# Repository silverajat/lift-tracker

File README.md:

# lift-tracker

A wrist wearable that counts reps, measures rep speed and quality, buzzes when a set has slowed too much or rest is over, and tells me when to add weight. The moment a set ends, the phone app shows the rep count and a quality score for each rep (speed, range, consistency). The same signal pipeline is also built in Verilog as an RTL project, verified against a Python golden model on my own gym data.

**Status:** D1 logger running on the XIAO in the printed pod (battery, auto-recording, USB dumps). Now: Bluetooth control from a phone app, so each set is started, stopped and labelled from the phone. Custom PCB v1.1 ready to order. The final Fitbit-sized pod v2 (7 mm thick, charges on the Fitbit Air charger) is designed and routed, waiting on nRF module stock: see `hardware/pod-v2/`.

*Pod v4: XIAO nRF52840 Sense + LiPo in a black PETG print, on a hook-and-loop strap, charging over USB-C through the side hole.*

## Layout

```
firmware/   Zephyr firmware for the XIAO nRF52840 Sense
  logger/     D1: records IMU data to flash, dumps CSV over USB
python/     golden model and analysis of my lift data
  tools/      dump_logs.py: pulls recordings off the board
hardware/   enclosure CAD (OpenSCAD), STLs, later the KiCad PCB
rtl/        Verilog + cocotb tests + formal proofs
app/        the phone app (later, D6)
docs/       logo, accuracy report, photos, demo video
data/       recordings (raw data is git-ignored)
```

## Build order

**Device:** D0 parts → D1 logger → D2 record lifts → D3 Python model → D4 video check → D5 real firmware + Bluetooth → D6 app → D7 buzz alerts → D8 custom PCB → D9 bring-up.

**RTL:** R1 UART + cocotb → R2 full pipeline → R3 formal proofs → R4 FPGA demo.

The full plan lives in my Lift Tracker Wearable doc.

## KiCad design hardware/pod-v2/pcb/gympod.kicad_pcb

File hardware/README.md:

# Hardware

## pod/ — gym prototype enclosure

OpenSCAD source (`lift_pod.scad`, all sizes are parameters at the top) and print-ready STLs for the base, separator and lid. Holds the XIAO nRF52840 Sense and a 302030 LiPo; a one-piece 20 mm loop band threads through a channel underneath.

Print: PETG (PLA for fit tests), 0.16–0.2 mm layers, 3 walls, no supports. Base floor-down with a brim, lid dome-up, separator flat.

To change a size: edit the number in `lift_pod.scad`, render (F6), export STL.

## pod-v2/ — the final, Fitbit-sized pod

36.2 × 20.2 × 7.0 mm. A custom 4-layer board (nRF52840 module, BMI270 IMU, 2 MB flash, 40 mAh LiPo, coin motor) that charges on the Google Fitbit Air charger. The board is the pod's underside: two gold contacts 18 mm apart plus a steel disc for the charger's magnet, with a bridge so it charges either way round. Everything else goes over Bluetooth.

- `SPEC.md`: decisions, circuit, pin map, parts, assembly.
- `pcb/`: the whole board as Python data (`design.py`, `placement.py`) → KiCad schematic, placement, staged Freerouting, DRC (`make_release.sh`).
- `release/liftpod_v2_revA/`: Gerbers, JLC BOM/CPL, renders, schematic PDF, checks, `README_ORDER.md`.
- `lift_pod_v2.scad` / `lift_pod_v2_shell.stl`: the one-piece shell for JLC3DP (SLA black resin).

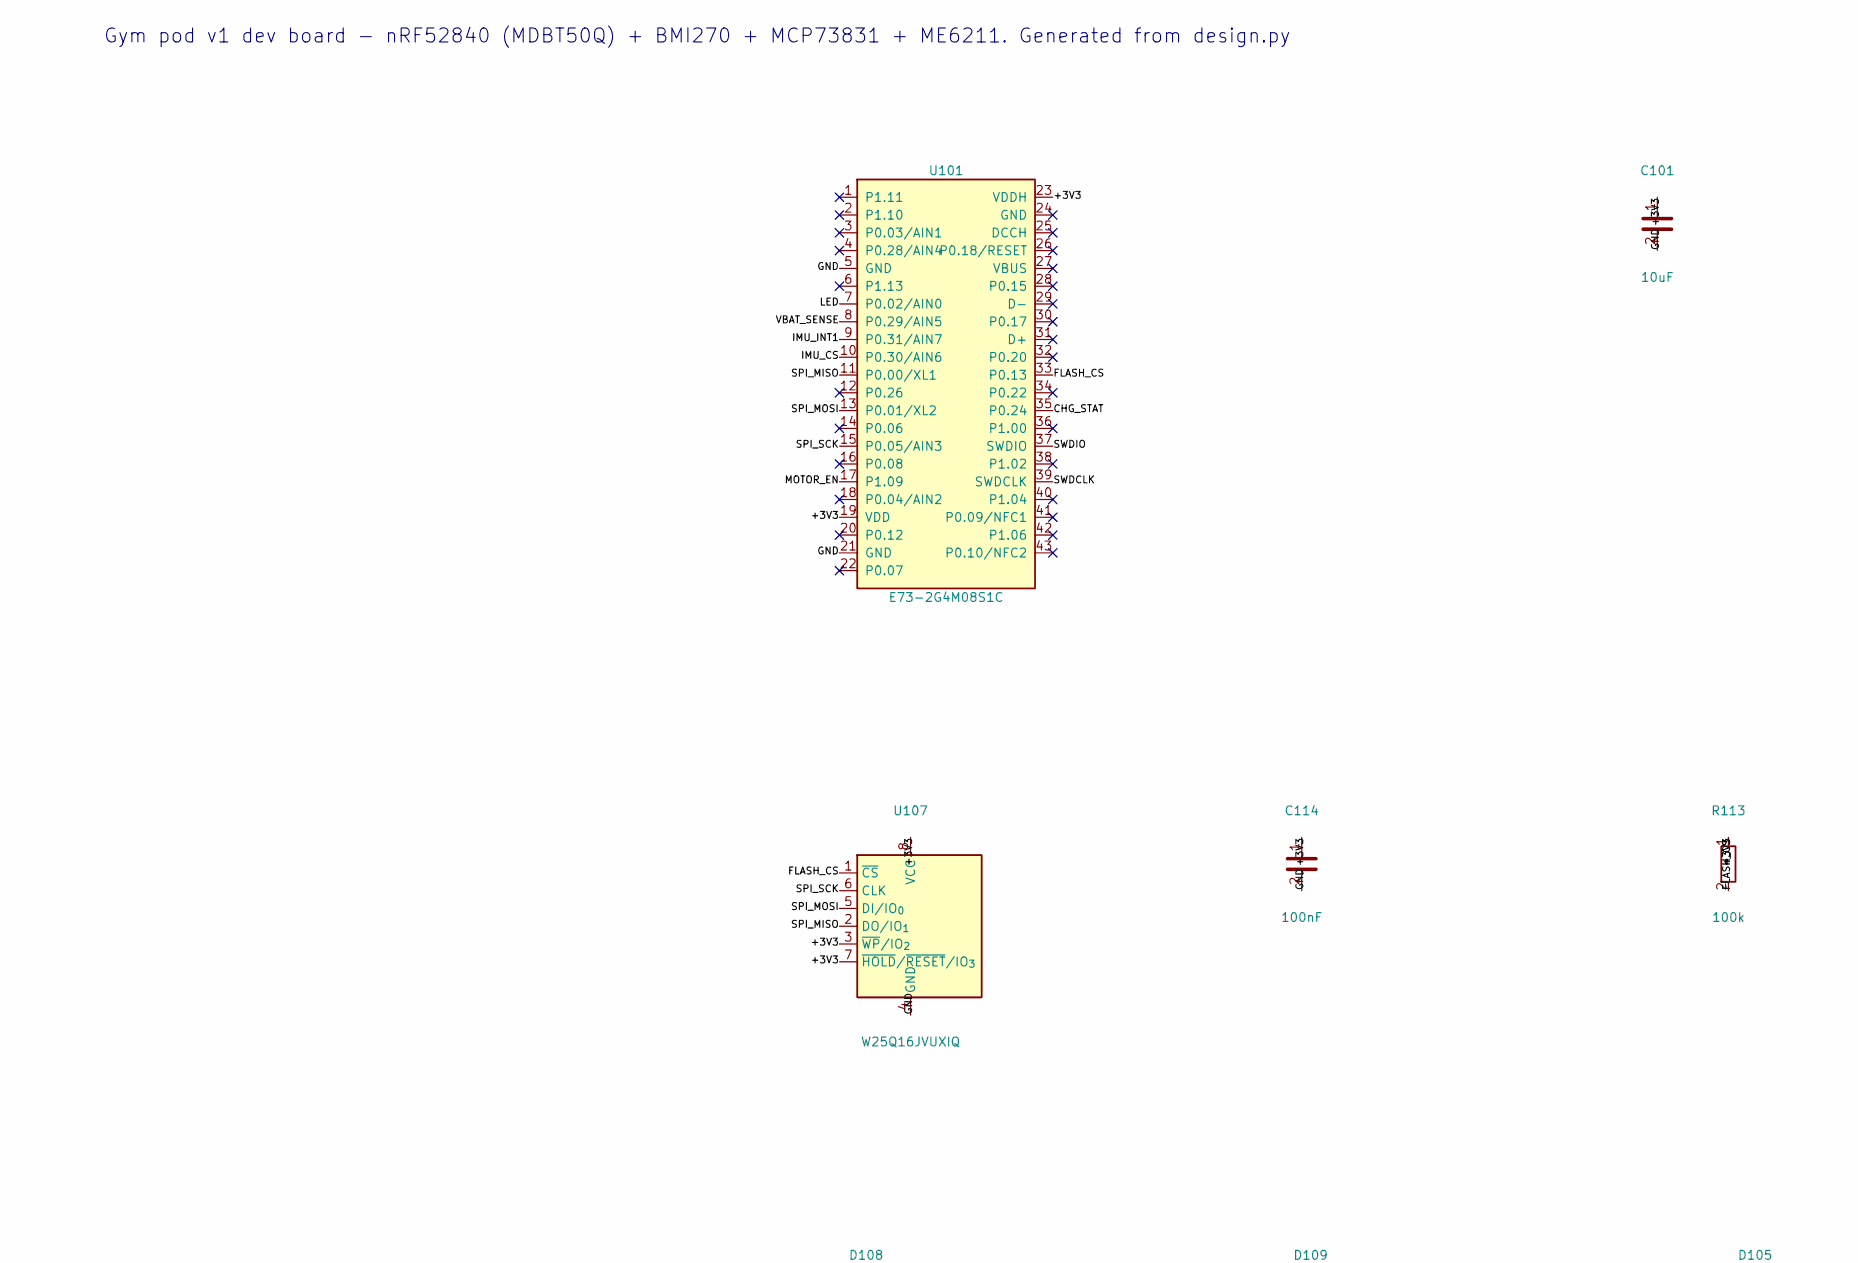
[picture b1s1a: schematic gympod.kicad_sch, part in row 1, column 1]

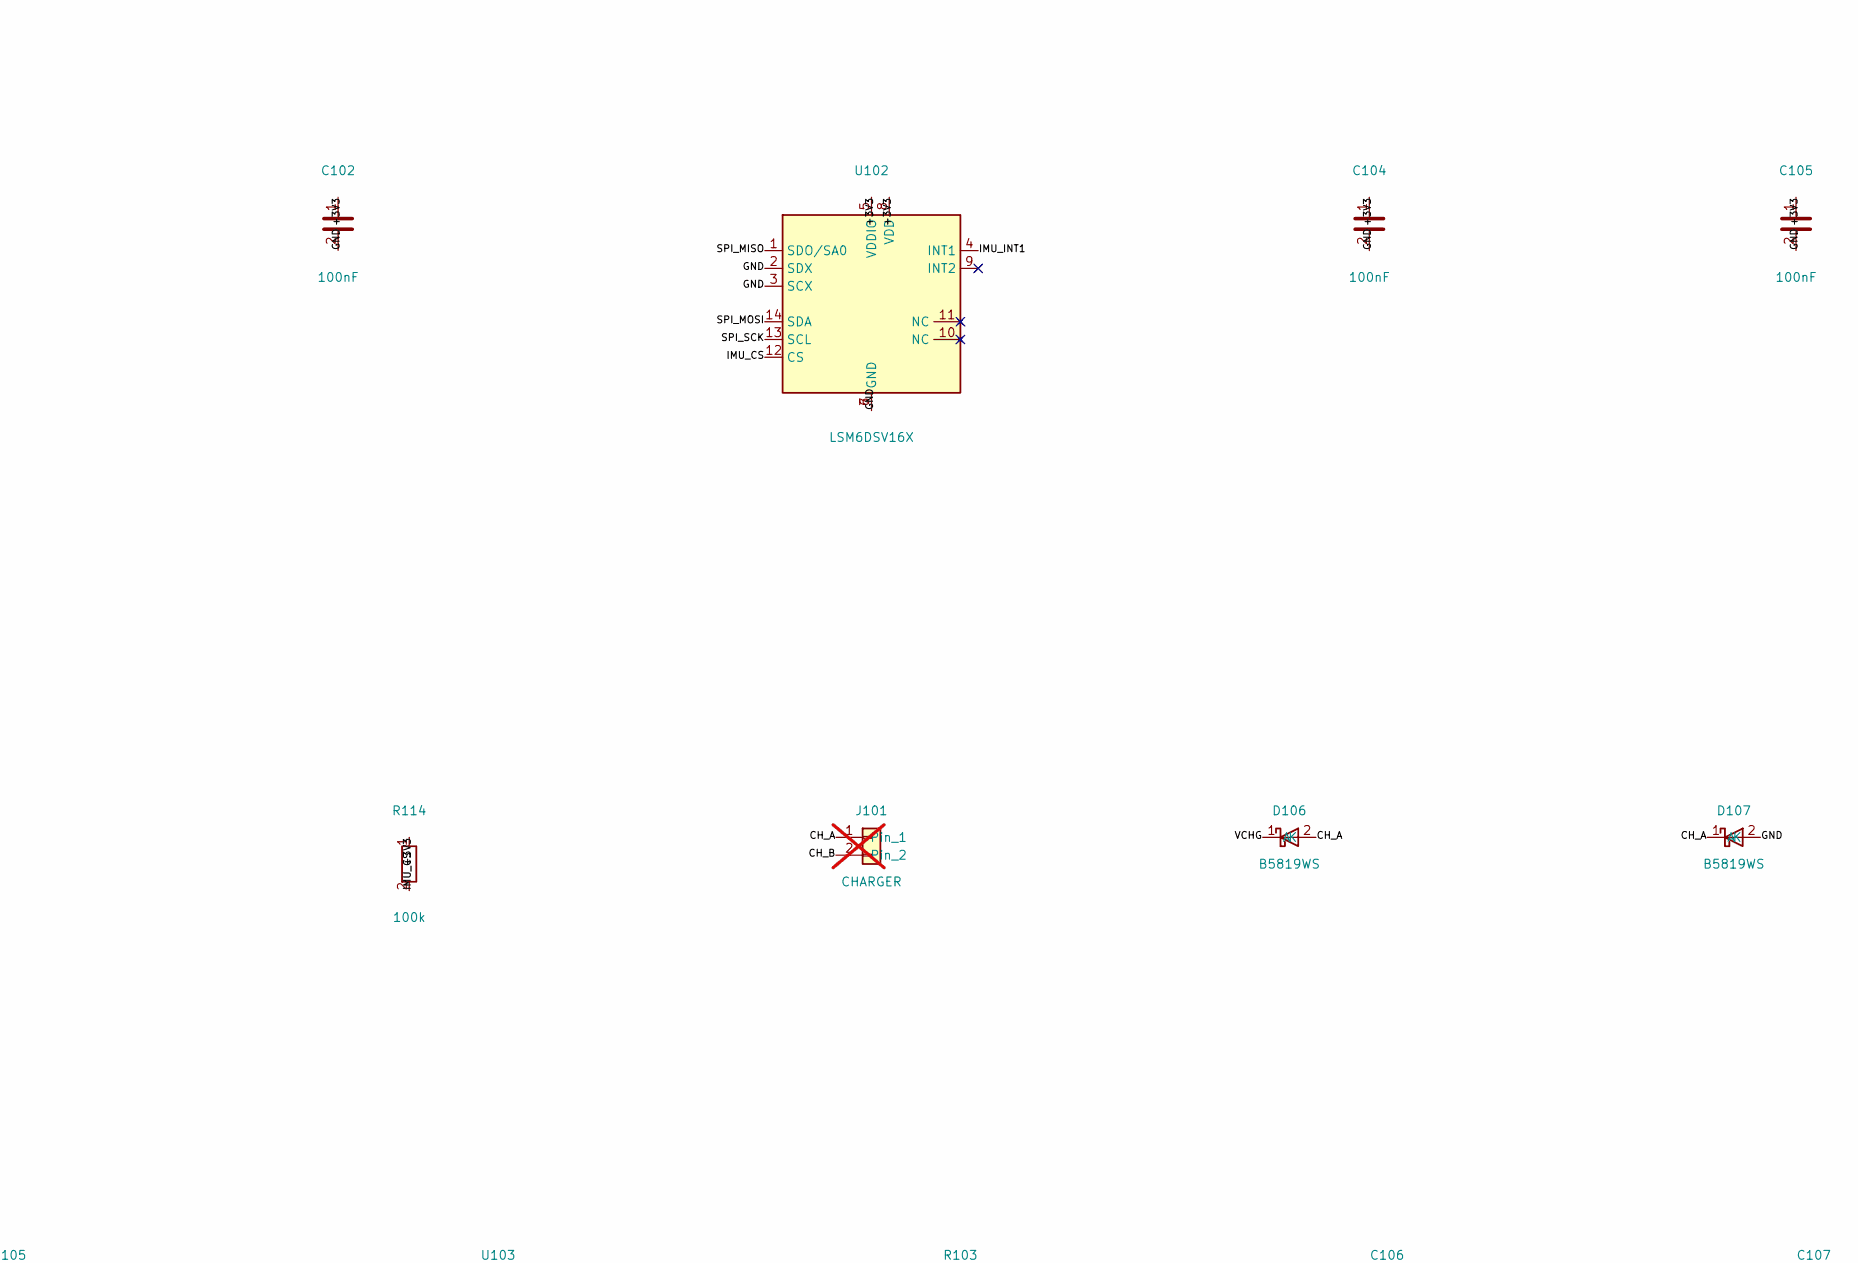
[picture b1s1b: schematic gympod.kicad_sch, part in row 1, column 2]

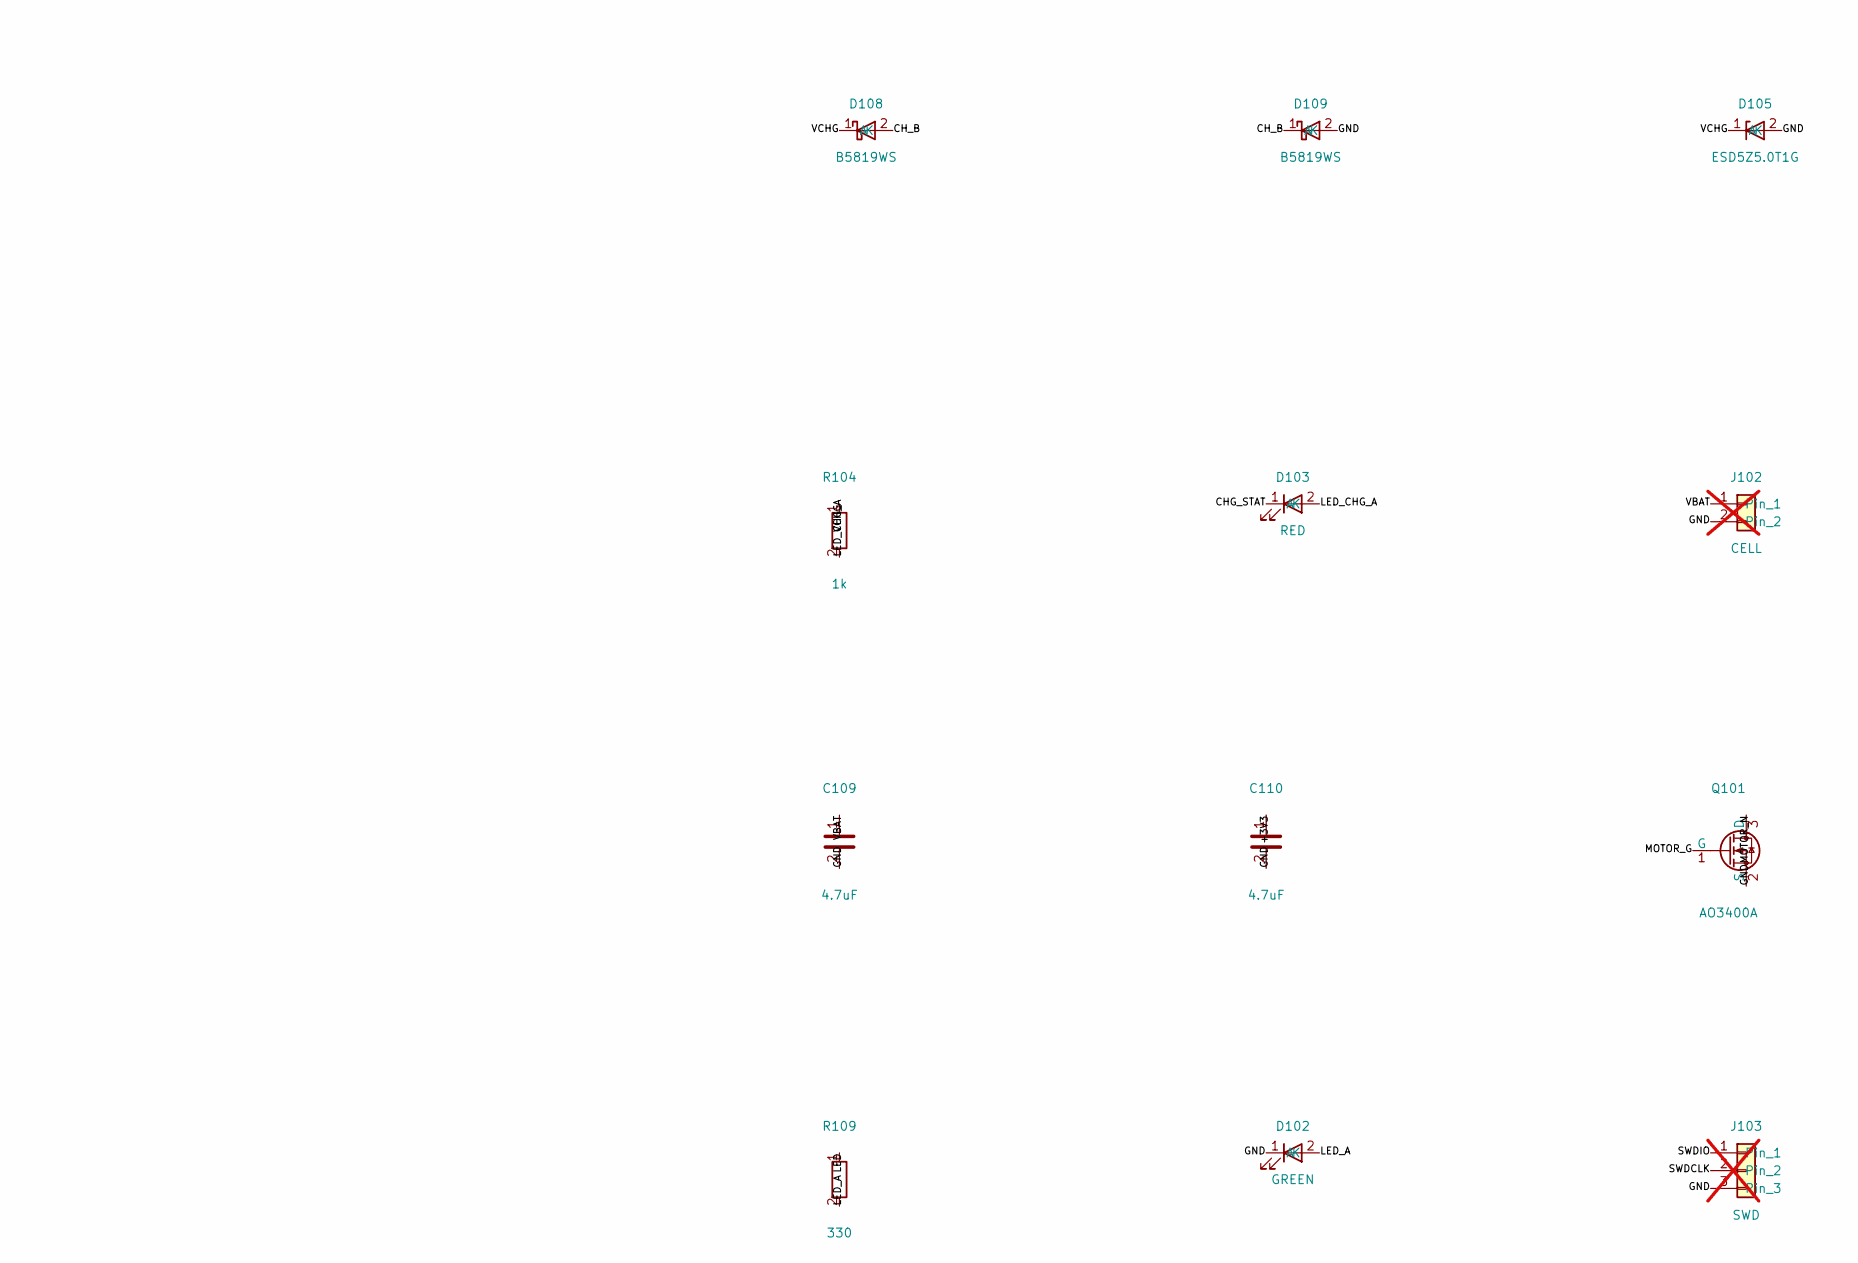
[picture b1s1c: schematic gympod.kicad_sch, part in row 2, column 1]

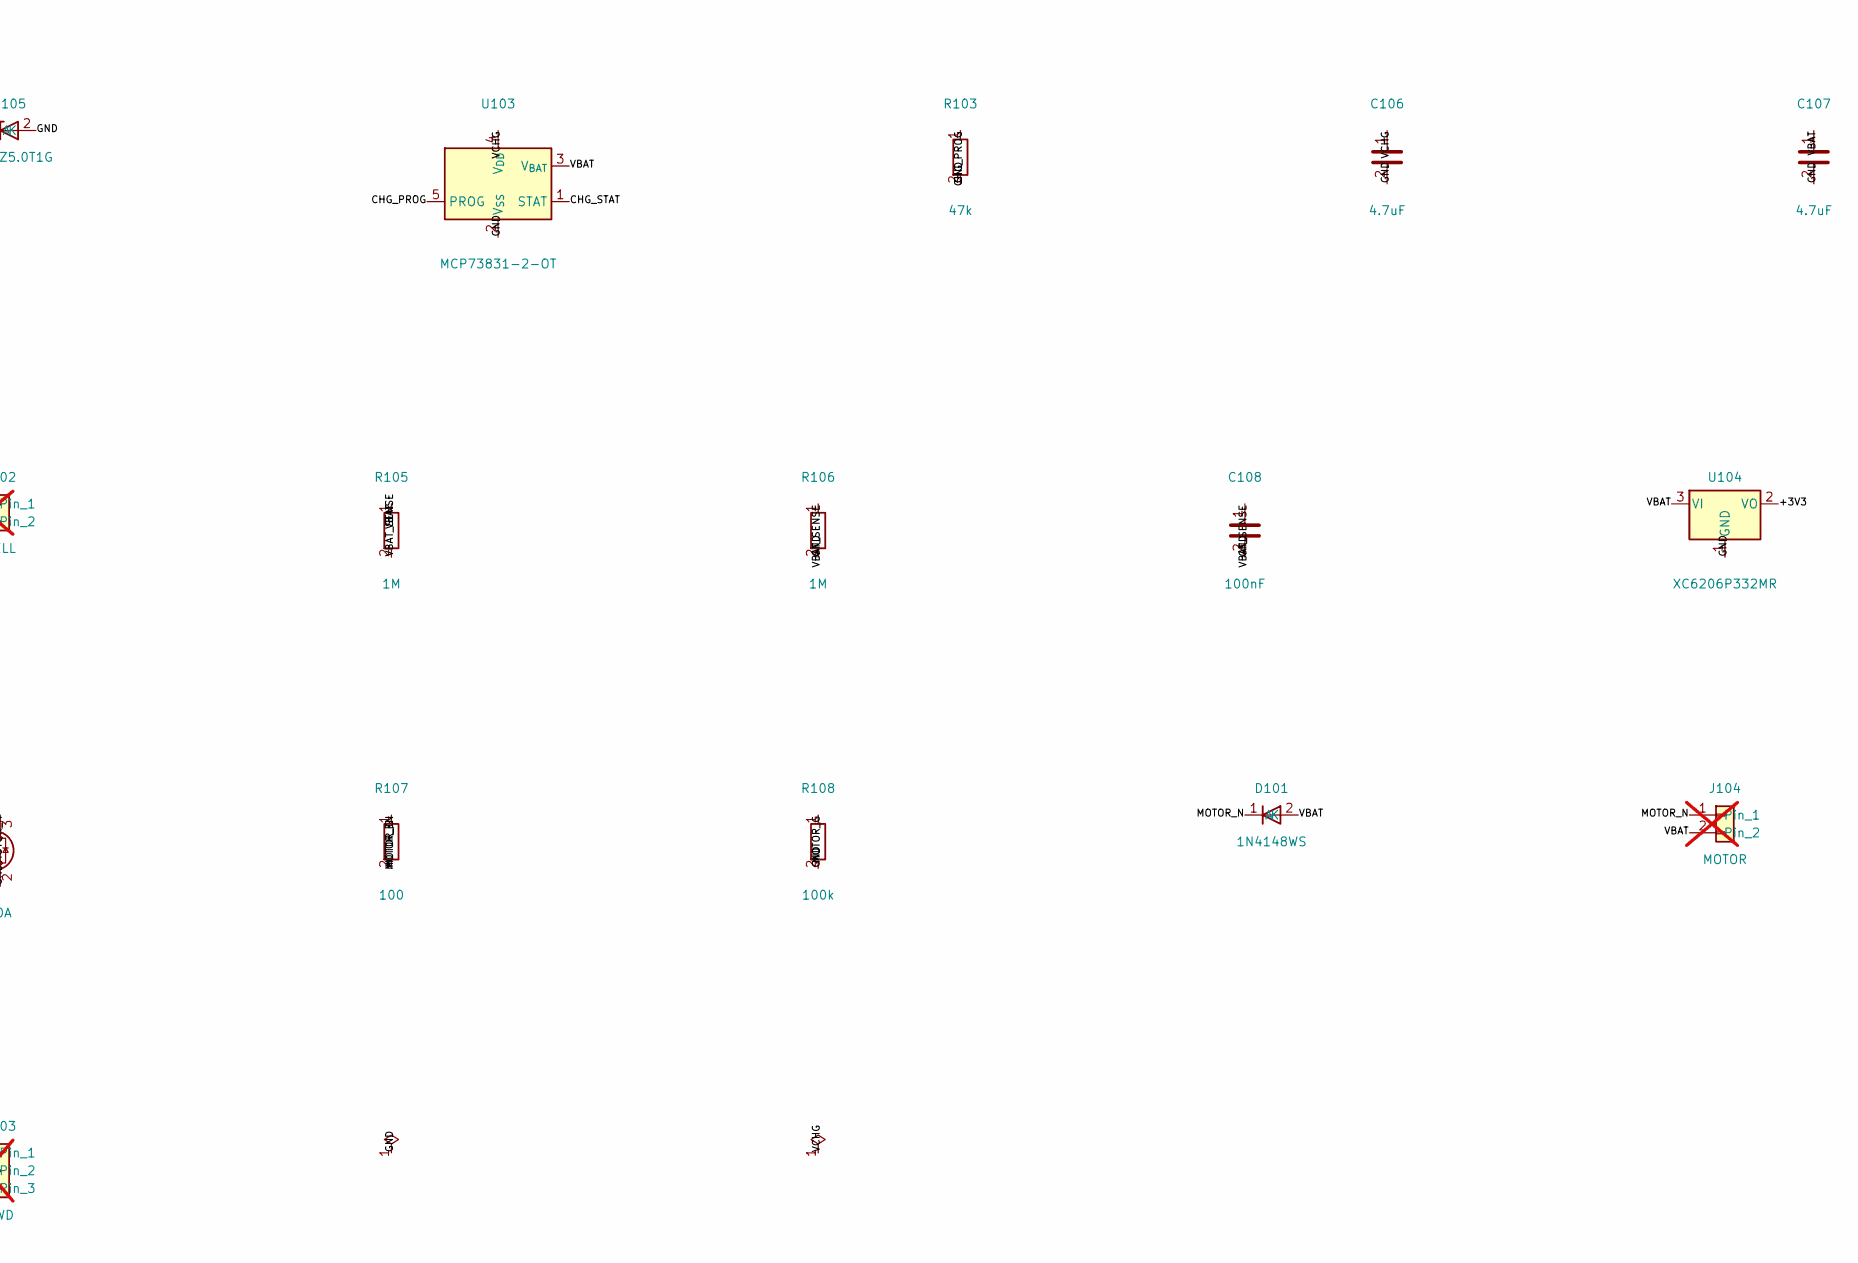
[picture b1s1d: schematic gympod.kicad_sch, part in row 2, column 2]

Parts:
C101: 10uF; C_0402_1005Metric; LCSC C15525
C102, C104, C105, C108, C114: 100nF; C_0402_1005Metric; LCSC C1525
C106, C107, C109, C110: 4.7uF; C_0402_1005Metric; LCSC C23733
D101: 1N4148WS; D_SOD-323; LCSC C2128
D102: GREEN; LED_0603_1608Metric; LCSC C12624
D103: RED; LED_0603_1608Metric; LCSC C2286
D105: ESD5Z5.0T1G; D_SOD-523; LCSC C82044
D106, D107, D108, D109: B5819WS; D_SOD-323; LCSC C22624
J101: CHARGER; Charger_Contacts_FitbitAir_P18mm; not fitted
J102: CELL; Cell_Pads_2x1.8x2.4mm_P3mm; not fitted
J103: SWD; SWD_Pads_1x03_P1.5mm; not fitted
J104: MOTOR; Motor_Pads_2x1.2x1.6mm_P2.5mm; not fitted
Q101: AO3400A; SOT-23; LCSC C20917
R103: 47k; R_0402_1005Metric; LCSC C25792
R104: 1k; R_0402_1005Metric; LCSC C11702
R105, R106: 1M; R_0402_1005Metric; LCSC C26083
R107: 100; R_0402_1005Metric; LCSC C25076
R108, R113, R114: 100k; R_0402_1005Metric; LCSC C25741
R109: 330; R_0402_1005Metric; LCSC C25104
U101: E73-2G4M08S1C; Ebyte_E73-2G4M08S1C; LCSC C356849
U102: LSM6DSV16X; LGA-14_3x2.5mm_P0.5mm_LayoutBorder3x4y; LCSC C5267406
U103: MCP73831-2-OT; SOT-23-5; LCSC C424093
U104: XC6206P332MR; SOT-23-3; LCSC C5446
U107: W25Q16JVUXIQ; Winbond_USON-8-1EP_2x3mm_P0.5mm; LCSC C2843335

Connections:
/+3V3: C101.1, C102.1, C104.1, C105.1, C110.1, C114.1, R113.1, R114.1, U101.19 (VDD), U101.23 (VDDH), U102.5 (VDDIO), U102.8 (VDD), U104.2 (VO), U107.3 (~WP/IO_{2}), U107.7 (~HOLD/~RESET/IO_{3}), U107.8 (VCC)
/CHG_PROG: R103.1, U103.5 (PROG)
/CHG_STAT: D103.1 (K), U101.35 (P0.24), U103.1 (STAT)
/CH_A: D106.2 (A), D107.1 (K), J101.1
/CH_B: D108.2 (A), D109.1 (K), J101.2
/FLASH_CS: R113.2, U101.33 (P0.13), U107.1 (~CS)
/GND: C101.2, C102.2, C104.2, C105.2, C106.2, C107.2, C108.2, C109.2, C110.2, C114.2, D102.1 (K), D105.2 (A), D107.2 (A), D109.2 (A), J102.2, J103.3, Q101.2 (S), R103.2, R106.2, R108.2, U101.5 (GND), U101.21 (GND), U102.2 (SDX), U102.3 (SCX), U102.6 (GND), U102.7 (GND), U103.2 (V_{SS}), U104.1 (GND), U107.4 (GND)
/IMU_CS: R114.2, U101.10 (P0.30/AIN6), U102.12 (CS)
/IMU_INT1: U101.9 (P0.31/AIN7), U102.4 (INT1)
/LED: R109.1, U101.7 (P0.02/AIN0)
/LED_A: D102.2 (A), R109.2
/LED_CHG_A: D103.2 (A), R104.2
/MOTOR_EN: R107.1, U101.17 (P1.09)
/MOTOR_G: Q101.1 (G), R107.2, R108.1
/MOTOR_N: D101.1 (K), J104.1, Q101.3 (D)
/SPI_MISO: U101.11 (P0.00/XL1), U102.1 (SDO/SA0), U107.2 (DO/IO_{1})
/SPI_MOSI: U101.13 (P0.01/XL2), U102.14 (SDA), U107.5 (DI/IO_{0})
/SPI_SCK: U101.15 (P0.05/AIN3), U102.13 (SCL), U107.6 (CLK)
/SWDCLK: J103.2, U101.39 (SWDCLK)
/SWDIO: J103.1, U101.37 (SWDIO)
/VBAT: C107.1, C109.1, D101.2 (A), J102.1, J104.2, R105.1, U103.3 (V_{BAT}), U104.3 (VI)
/VBAT_SENSE: C108.1, R105.2, R106.1, U101.8 (P0.29/AIN5)
/VCHG: C106.1, D105.1 (K), D106.1 (K), D108.1 (K), R104.1, U103.4 (V_{DD})

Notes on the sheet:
Gym pod v1 dev board - nRF52840 (MDBT50Q) + BMI270 + MCP73831 + ME6211. Generated from design.py

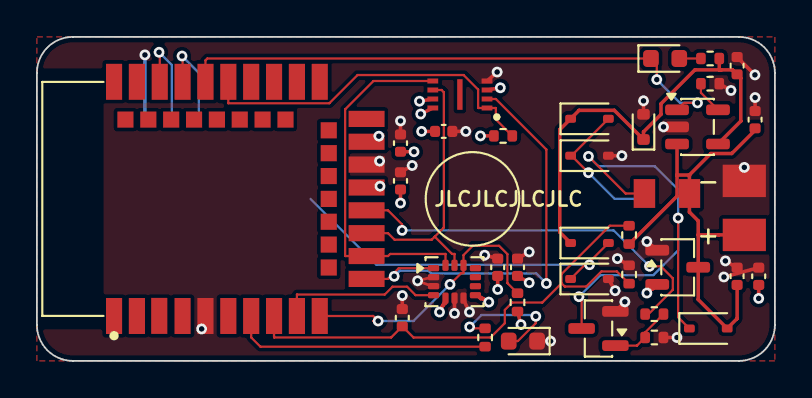
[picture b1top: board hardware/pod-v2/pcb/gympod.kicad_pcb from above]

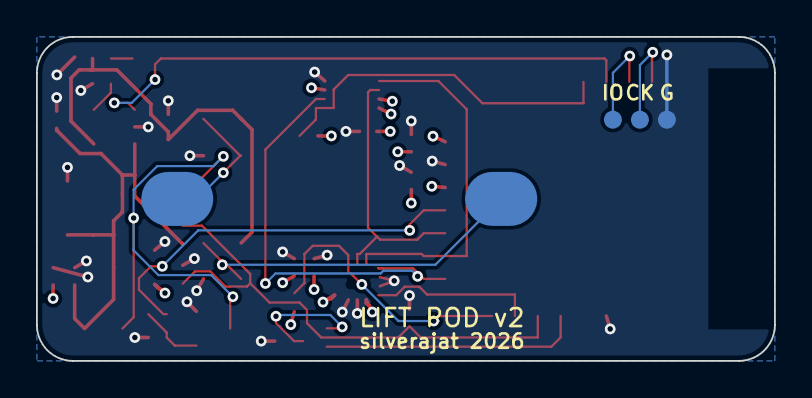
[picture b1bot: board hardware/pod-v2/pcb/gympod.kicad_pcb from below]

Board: 4 copper layers, 41.0 x 18.0 mm, 38 parts (2 on the bottom side), 23 nets.

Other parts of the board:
MK1: Steel_Target_D5mm
